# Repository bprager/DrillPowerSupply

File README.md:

# DrillPowerSupply
PWM Controller for Drill Spindle

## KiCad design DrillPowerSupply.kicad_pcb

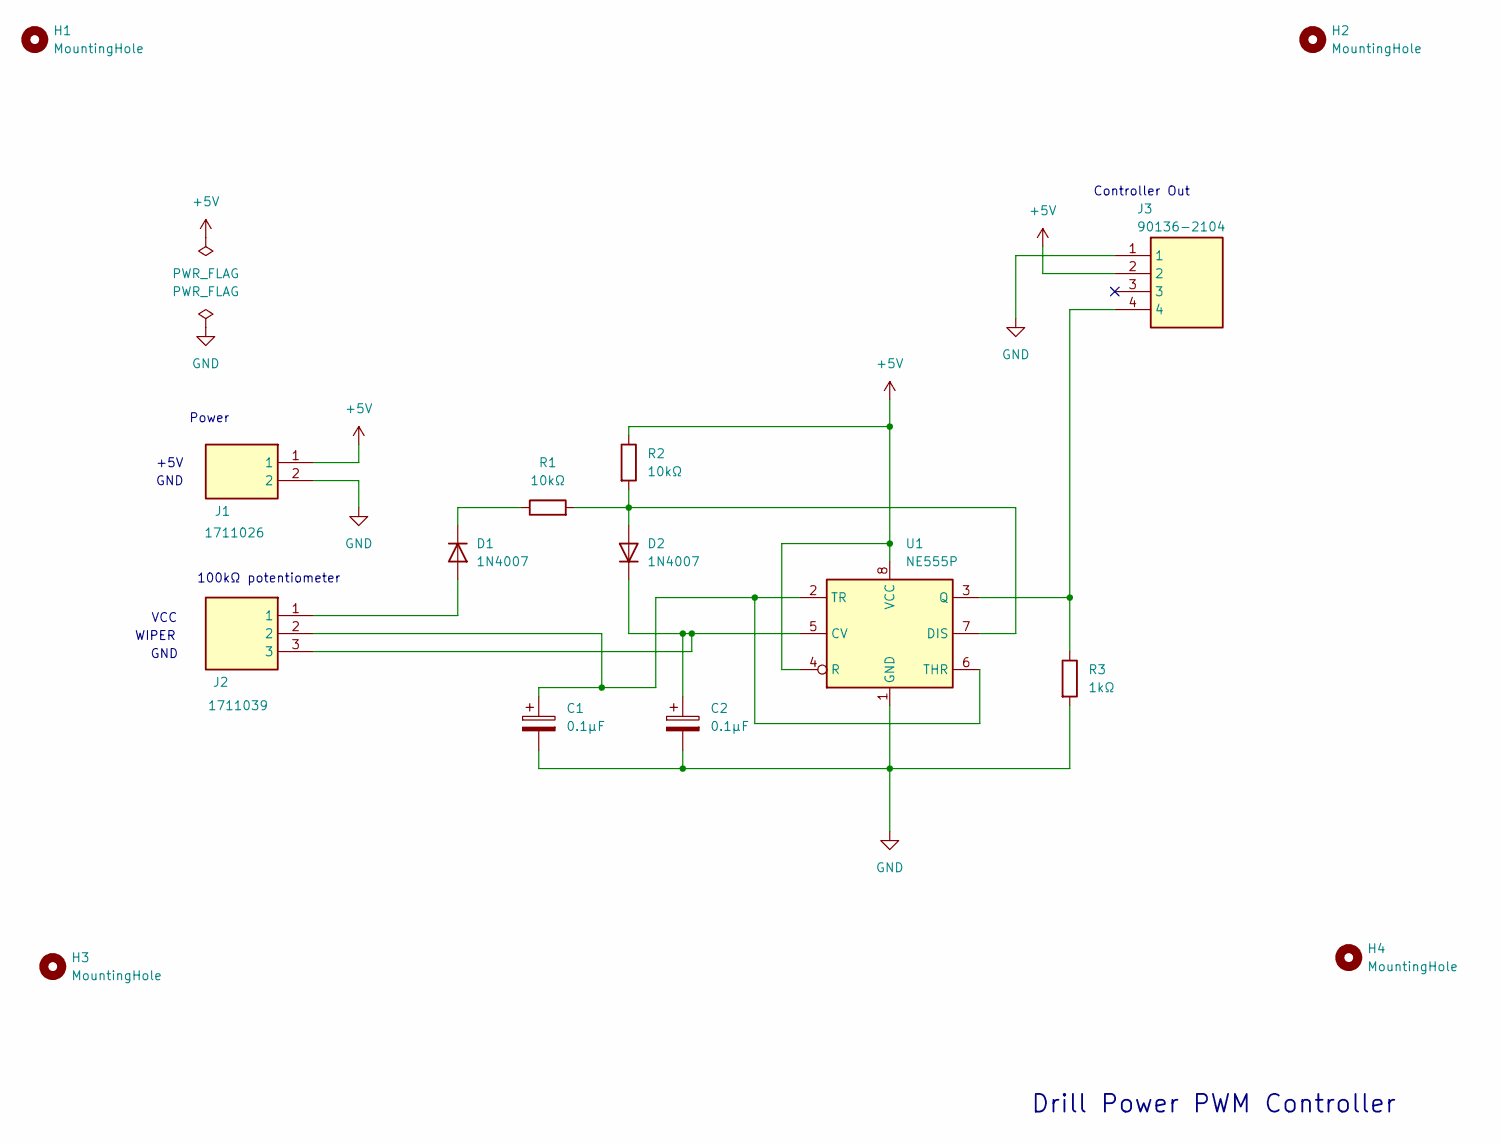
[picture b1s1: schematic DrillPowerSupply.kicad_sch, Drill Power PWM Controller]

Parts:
C1, C2: 0.1μF; C_Radial_D4.0mm_H7.0mm_P1.50mm
D1, D2: 1N4007; D_DO-41_SOD81_P10.16mm_Horizontal
H1, H2, H3, H4: MountingHole; MountingHole_3.2mm_M3_Pad_Via
J1: 1711026; Phoenix_Terminal_Block_2_Pos; Mouser Part Number 651-1711026
J2: 1711039; Phoenix_Terminal_Block_3_Pos; Mouser Part Number 651-1711039
J3: 90136-2104; SHDRRA4W65P0X254_1X4_1351X1090X751P; Mouser Part Number 538-90136-2104
R1, R2: 10kΩ; R_Axial_DIN0207_L6.3mm_D2.5mm_P7.62mm_Horizontal
R3: 1kΩ; R_Axial_DIN0207_L6.3mm_D2.5mm_P7.62mm_Horizontal
U1: NE555P; DIP-8_W7.62mm

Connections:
+5V: J1.1, J3.2, R2.1, U1.4 (R), U1.8 (VCC)
GND: C1.2, C2.2, J1.2, J3.1, R3.2, U1.1 (GND)
unnamed: D1.2 (A), J2.1
unnamed: D1.1 (K), R1.1
unnamed: D2.2 (A), R1.2, R2.2, U1.7 (DIS)
unnamed: C2.1, D2.1 (K), J2.3, U1.5 (CV)
unnamed: J3.4, R3.1, U1.3 (Q)
unnamed: C1.1, J2.2, U1.2 (TR), U1.6 (THR)

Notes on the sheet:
GND
Controller Out
WIPER
VCC
Drill Power PWM Controller
+5V
Power
100kΩ potentiometer

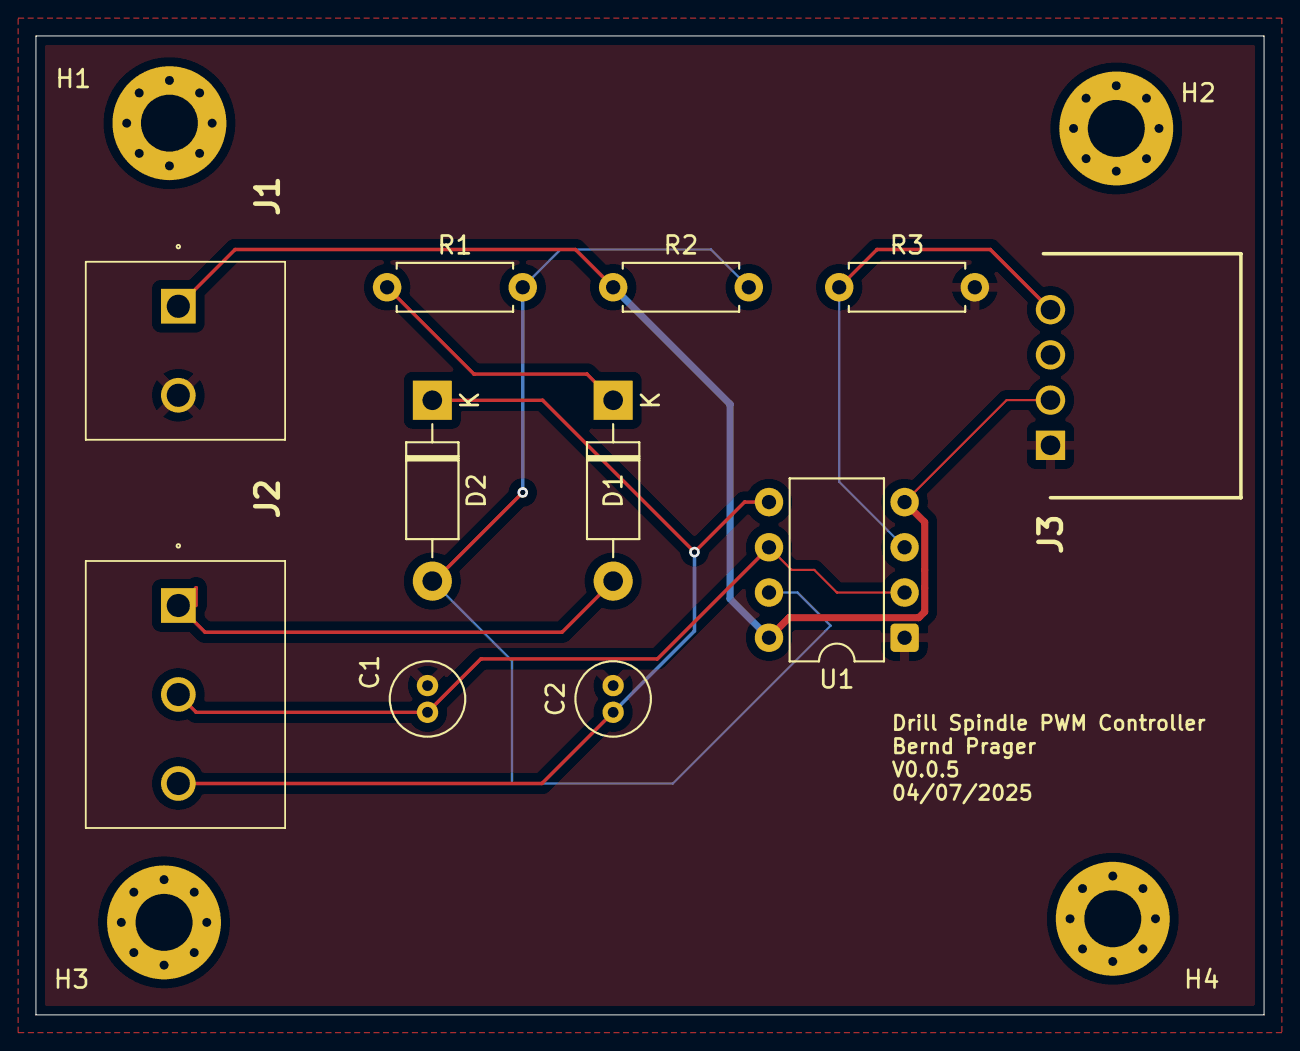
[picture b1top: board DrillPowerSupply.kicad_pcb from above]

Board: 4 copper layers, 69.0 x 55.0 mm, 15 parts (0 on the bottom side), 8 nets.

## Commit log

2025-04-07 initial version
2025-04-08 PCB done
2025-04-10 ordered
